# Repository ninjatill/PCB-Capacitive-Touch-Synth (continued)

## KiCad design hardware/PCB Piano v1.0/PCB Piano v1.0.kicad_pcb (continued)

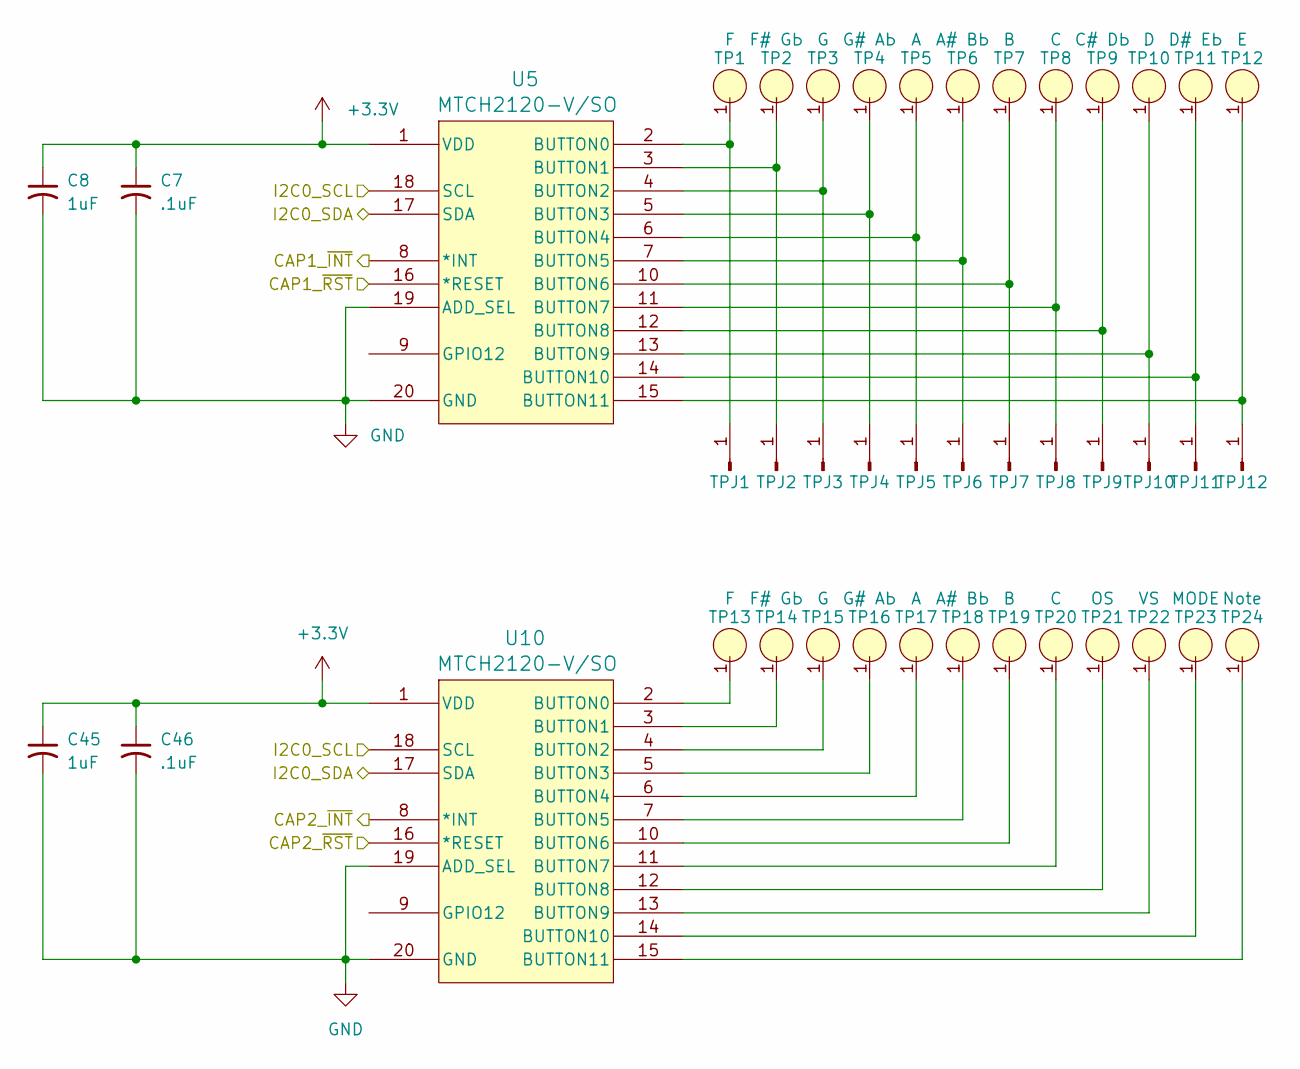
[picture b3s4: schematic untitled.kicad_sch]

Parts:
C7, C46: .1uF; C_0603_1608Metric
C8, C45: 1uF; C_0603_1608Metric
TP1, TP13: F; Touchpad_WhiteKey
TP2, TP14: F# GЬ; Touchpad_BlackKey
TP3, TP15: G; Touchpad_WhiteKey
TP4, TP16: G# AЬ; Touchpad_BlackKey
TP5, TP17: A; Touchpad_WhiteKey
TP6, TP18: A# BЬ; Touchpad_BlackKey
TP7, TP19: B; Touchpad_WhiteKey
TP8, TP20: C; Touchpad_WhiteKey
TP9: C# DЬ; Touchpad_BlackKey
TP10: D; Touchpad_WhiteKey
TP11: D# EЬ; Touchpad_BlackKey
TP12: E; Touchpad_WhiteKey
TP21: OS; Touchpad_Circle_10mm
TP22: VS; Touchpad_Circle_10mm
TP23: MODE; Touchpad_Circle_10mm
TP24: Note
TPJ1, TPJ2, TPJ3, TPJ4, TPJ5, TPJ6, TPJ7, TPJ8, TPJ9, TPJ10, TPJ11, TPJ12: Conn_01x01_Pin
U5, U10: MTCH2120-V/SO; SOIC-20W_7.5x12.8mm_P1.27mm

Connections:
+3.3V: C7.1, C8.1, C45.1, C46.1, U5.1 (VDD), U10.1 (VDD); also elsewhere on the board
/MCU/CAP1_~INT: U5.8 (*INT); also elsewhere on the board
/MCU/CAP1_~RST: U5.16 (*RESET); also elsewhere on the board
/MCU/CAP2_~INT: U10.8 (*INT); also elsewhere on the board
/MCU/CAP2_~RST: U10.16 (*RESET); also elsewhere on the board
/MCU/I2C0_SCL: U5.18 (SCL), U10.18 (SCL); also elsewhere on the board
/MCU/I2C0_SDA: U5.17 (SDA), U10.17 (SDA); also elsewhere on the board
GND: C7.2, C8.2, C45.2, C46.2, U5.19 (ADD_SEL), U5.20 (GND), U10.19 (ADD_SEL), U10.20 (GND); also elsewhere on the board
unnamed: TP1.1, TPJ1.1, U5.2 (BUTTON0)
unnamed: TP2.1, TPJ2.1, U5.3 (BUTTON1)
unnamed: TP3.1, TPJ3.1, U5.4 (BUTTON2)
unnamed: TP4.1, TPJ4.1, U5.5 (BUTTON3)
unnamed: TP5.1, TPJ5.1, U5.6 (BUTTON4)
unnamed: TP6.1, TPJ6.1, U5.7 (BUTTON5)
unnamed: TP7.1, TPJ7.1, U5.10 (BUTTON6)
unnamed: TP8.1, TPJ8.1, U5.11 (BUTTON7)
unnamed: TP9.1, TPJ9.1, U5.12 (BUTTON8)
unnamed: TP10.1, TPJ10.1, U5.13 (BUTTON9)
unnamed: TP11.1, TPJ11.1, U5.14 (BUTTON10)
unnamed: TP12.1, TPJ12.1, U5.15 (BUTTON11)
unnamed: TP13.1, U10.2 (BUTTON0)
unnamed: TP14.1, U10.3 (BUTTON1)
unnamed: TP15.1, U10.4 (BUTTON2)
unnamed: TP16.1, U10.5 (BUTTON3)
unnamed: TP17.1, U10.6 (BUTTON4)
unnamed: TP18.1, U10.7 (BUTTON5)
unnamed: TP19.1, U10.10 (BUTTON6)
unnamed: TP20.1, U10.11 (BUTTON7)
unnamed: TP21.1, U10.12 (BUTTON8)
unnamed: TP22.1, U10.13 (BUTTON9)
unnamed: TP23.1, U10.14 (BUTTON10)
unnamed: TP24.1, U10.15 (BUTTON11)

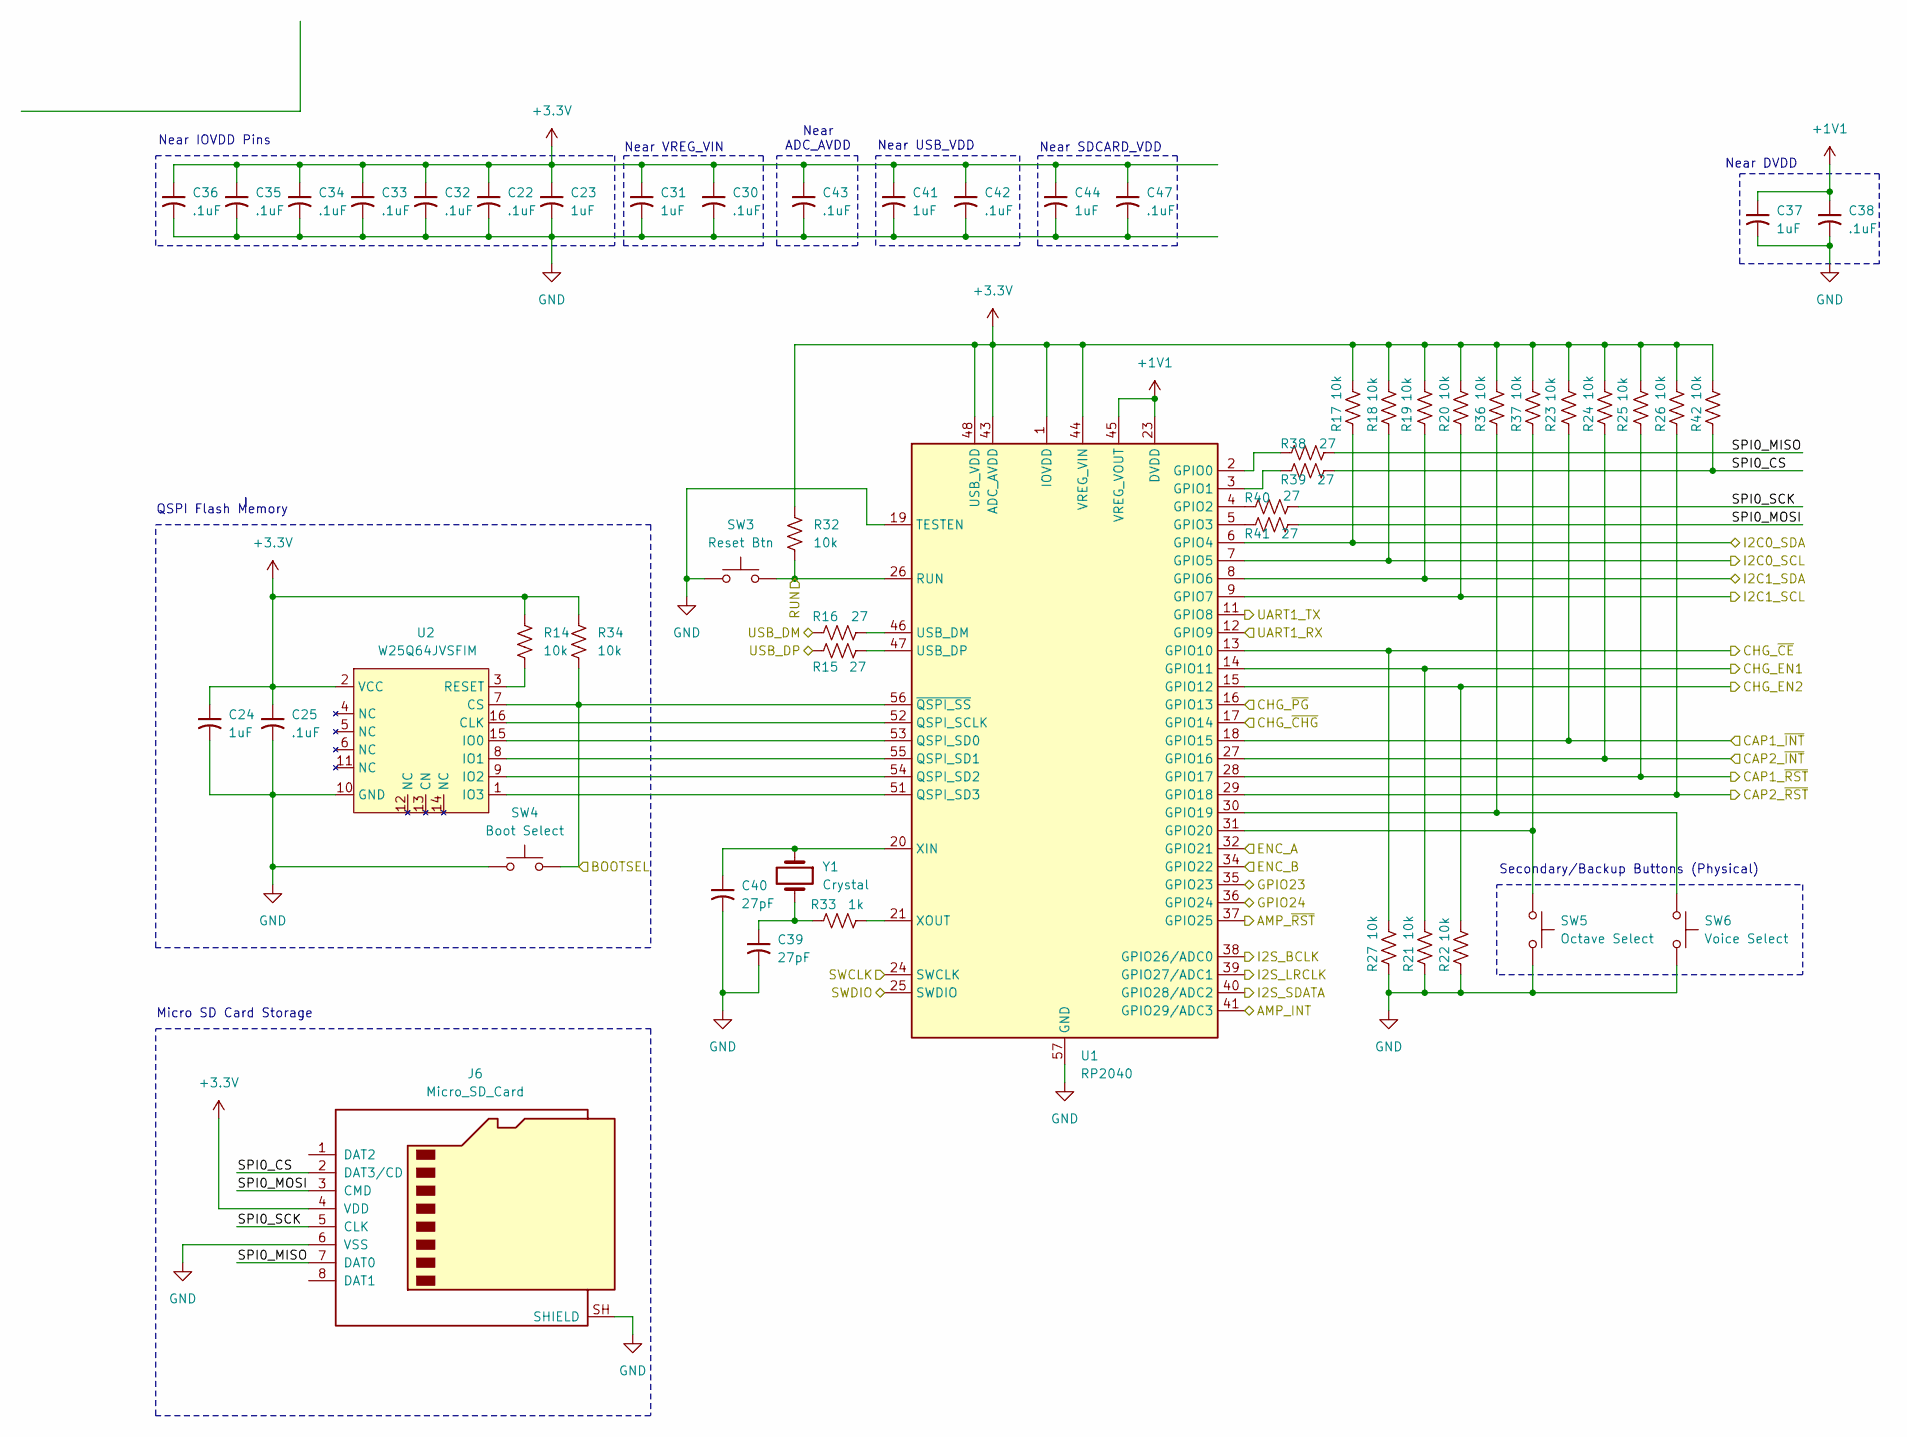
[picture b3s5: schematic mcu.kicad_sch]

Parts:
C22, C25, C30, C32, C33, C34, C35, C36, C38, C42, C43, C47: .1uF; C_0603_1608Metric
C23, C24, C31, C37, C41, C44: 1uF; C_0603_1608Metric
C39, C40: 27pF; C_0603_1608Metric
J6: Micro_SD_Card; microSD_HC_Hirose_DM3D-SF
R14, R17, R18, R19, R20, R21, R22, R23, R24, R25, R26, R27, R32, R34, R36, R37, R42: 10k; R_0603_1608Metric
R15, R16, R38, R39, R40, R41: 27; R_0603_1608Metric
R33: 1k; R_0603_1608Metric
SW3: Reset Btn; Button_Push_KMR6
SW4: Boot Select; Button_Push_KMR6
SW5: Octave Select; Button_Push_KMR6
SW6: Voice Select; Button_Push_KMR6
U1: RP2040; QFN-56-1EP_7x7mm_P0.4mm_EP3.2x3.2mm
U2: W25Q64JVSFIM; SOIC-16W_7.5x10.3mm_P1.27mm
Y1: Crystal; Crystal_SMD_Abracon_ABM8G-4Pin_3.2x2.5mm

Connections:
+1V1: C37.1, C38.1, U1.23 (DVDD), U1.45 (VREG_VOUT), U1.50 (DVDD)
+3.3V: C22.1, C23.1, C24.1, C25.1, C30.1, C31.1, C32.1, C33.1, C34.1, C35.1, C36.1, C41.1, C42.1, C43.1, C44.1, C47.1, J6.4 (VDD), R14.1, R17.1, R18.1, R19.1, R20.1, R23.1, R24.1, R25.1, R26.1, R32.1, R34.1, R36.1, R37.1, R42.1, U1.1 (IOVDD), U1.10 (IOVDD), U1.22 (IOVDD), U1.33 (IOVDD), U1.42 (IOVDD), U1.43 (ADC_AVDD), U1.44 (VREG_VIN), U1.48 (USB_VDD), U1.49 (IOVDD), U2.2 (VCC); also elsewhere on the board
/LED/I2C1_SCL: R20.2, U1.9 (GPIO7); also elsewhere on the board
/LED/I2C1_SDA: R19.2, U1.8 (GPIO6); also elsewhere on the board
/MCU/AMP_INT: U1.41 (GPIO29/ADC3); also elsewhere on the board
/MCU/AMP_~RST: U1.37 (GPIO25); also elsewhere on the board
/MCU/BOOTSEL: R34.2, SW4.2, U1.56 (~QSPI_SS), U2.7 (CS); also elsewhere on the board
/MCU/CAP1_~INT: R23.2, U1.18 (GPIO15); also elsewhere on the board
/MCU/CAP1_~RST: R25.2, U1.28 (GPIO17); also elsewhere on the board
/MCU/CAP2_~INT: R24.2, U1.27 (GPIO16); also elsewhere on the board
/MCU/CAP2_~RST: R26.2, U1.29 (GPIO18); also elsewhere on the board
/MCU/CHG_EN1: R21.1, U1.14 (GPIO11); also elsewhere on the board
/MCU/CHG_EN2: R22.1, U1.15 (GPIO12); also elsewhere on the board
/MCU/CHG_~CE: R27.1, U1.13 (GPIO10); also elsewhere on the board
/MCU/CHG_~CHG: U1.17 (GPIO14); also elsewhere on the board
/MCU/CHG_~PG: U1.16 (GPIO13); also elsewhere on the board
/MCU/ENC_A: U1.32 (GPIO21); also elsewhere on the board
/MCU/ENC_B: U1.34 (GPIO22); also elsewhere on the board
/MCU/GPIO23: U1.35 (GPIO23); also elsewhere on the board
/MCU/GPIO24: U1.36 (GPIO24); also elsewhere on the board
/MCU/I2C0_SCL: R18.2, U1.7 (GPIO5); also elsewhere on the board
/MCU/I2C0_SDA: R17.2, U1.6 (GPIO4); also elsewhere on the board
/MCU/I2S_BCLK: U1.38 (GPIO26/ADC0); also elsewhere on the board
/MCU/I2S_LRCLK: U1.39 (GPIO27/ADC1); also elsewhere on the board
/MCU/I2S_SDATA: U1.40 (GPIO28/ADC2); also elsewhere on the board
/MCU/SPI0_CS: J6.2 (DAT3/CD), R39.1, R42.2
/MCU/SPI0_MISO: J6.7 (DAT0), R38.1
/MCU/SPI0_MOSI: J6.3 (CMD), R41.1
/MCU/SPI0_SCK: J6.5 (CLK), R40.1
/MCU/SWCLK: U1.24 (SWCLK); also elsewhere on the board
/MCU/UART1_RX: U1.12 (GPIO9); also elsewhere on the board
/MCU/UART1_TX: U1.11 (GPIO8); also elsewhere on the board
/MCU/USB_DM: R16.2; also elsewhere on the board
/MCU/USB_DP: R15.2; also elsewhere on the board
/debug/RUN: R32.2, SW3.2, U1.26 (RUN); also elsewhere on the board
/debug/SWDIO: U1.25 (SWDIO); also elsewhere on the board
GND: C22.2, C23.2, C24.2, C25.2, C30.2, C31.2, C32.2, C33.2, C34.2, C35.2, C36.2, C37.2, C38.2, C39.2, C40.2, C41.2, C42.2, C43.2, C44.2, C47.2, J6.6 (VSS), J6.SH (SHIELD), R21.2, R22.2, R27.2, SW3.1, SW4.1, SW5.2, SW6.2, U1.19 (TESTEN), U1.57 (GND), U2.10 (GND); also elsewhere on the board
unnamed: C39.1, R33.1, Y1.2
unnamed: R38.2, U1.2 (GPIO0)
unnamed: R39.2, U1.3 (GPIO1)
unnamed: R40.2, U1.4 (GPIO2)
unnamed: R41.2, U1.5 (GPIO3)
unnamed: R36.2, SW6.1, U1.30 (GPIO19)
unnamed: R37.2, SW5.1, U1.31 (GPIO20)
unnamed: U1.52 (QSPI_SCLK), U2.16 (CLK)
unnamed: U1.53 (QSPI_SD0), U2.15 (IO0)
unnamed: U1.55 (QSPI_SD1), U2.8 (IO1)
unnamed: U1.54 (QSPI_SD2), U2.9 (IO2)
unnamed: U1.51 (QSPI_SD3), U2.1 (IO3)
unnamed: R16.1, U1.46 (USB_DM)
unnamed: R15.1, U1.47 (USB_DP)
unnamed: C40.1, U1.20 (XIN), Y1.1
unnamed: R33.2, U1.21 (XOUT)
unnamed: R14.2, U2.3 (RESET)

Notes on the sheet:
Near VREG_VIN
Near DVDD
Near IOVDD Pins
Secondary/Backup Buttons (Physical)
Micro SD Card Storage
Near USB_VDD
Near ADC_AVDD
Near SDCARD_VDD
QSPI Flash Memory

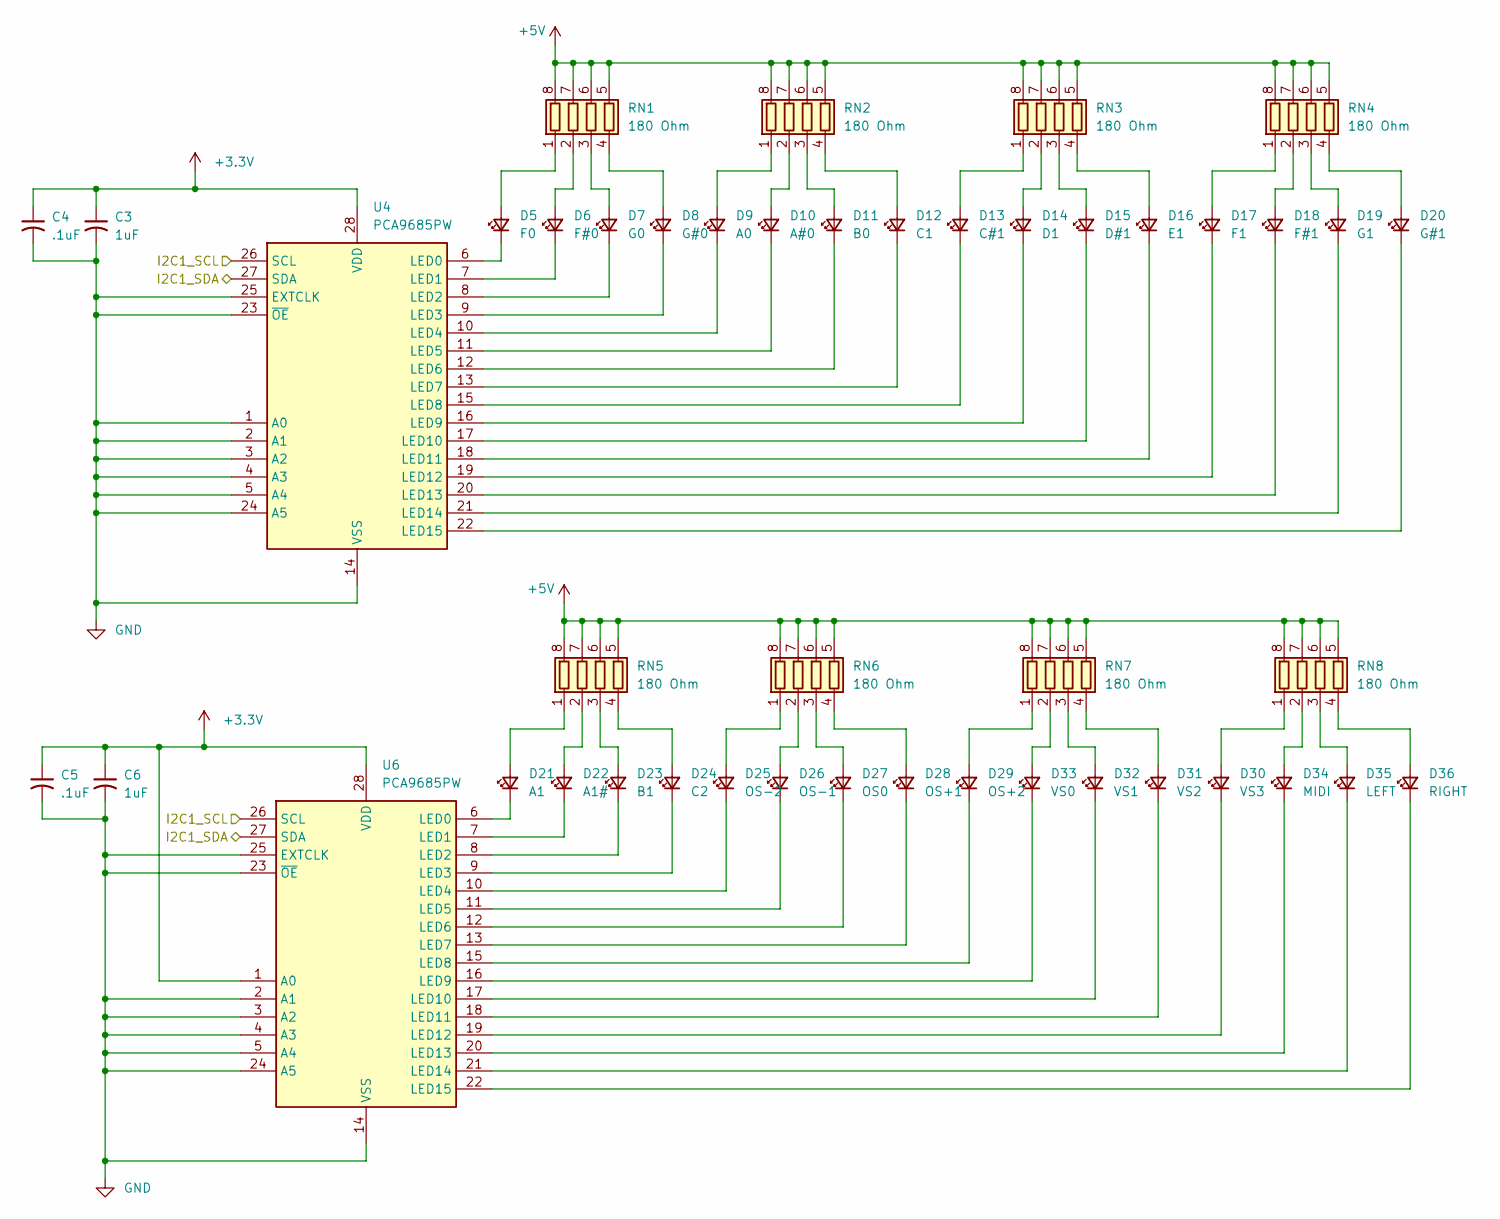
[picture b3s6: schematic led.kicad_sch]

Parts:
C3, C6: 1uF; C_0603_1608Metric
C4, C5: .1uF; C_0603_1608Metric
D5: F0; LED_0603_1608Metric
D6: F#0; LED_0603_1608Metric
D7: G0; LED_0603_1608Metric
D8: G#0; LED_0603_1608Metric
D9: A0; LED_0603_1608Metric
D10: A#0; LED_0603_1608Metric
D11: B0; LED_0603_1608Metric
D12: C1; LED_0603_1608Metric
D13: C#1; LED_0603_1608Metric
D14: D1; LED_0603_1608Metric
D15: D#1; LED_0603_1608Metric
D16: E1; LED_0603_1608Metric
D17: F1; LED_0603_1608Metric
D18: F#1; LED_0603_1608Metric
D19: G1; LED_0603_1608Metric
D20: G#1; LED_0603_1608Metric
D21: A1; LED_0603_1608Metric
D22: A1#; LED_0603_1608Metric
D23: B1; LED_0603_1608Metric
D24: C2; LED_0603_1608Metric
D25: OS-2; LED_0603_1608Metric
D26: OS-1; LED_0603_1608Metric
D27: OS0; LED_0603_1608Metric
D28: OS+1; LED_0603_1608Metric
D29: OS+2; LED_0603_1608Metric
D30: VS3; LED_0603_1608Metric
D31: VS2; LED_0603_1608Metric
D32: VS1; LED_0603_1608Metric
D33: VS0; LED_0603_1608Metric
D34: MIDI; LED_0603_1608Metric
D35: LEFT; LED_0603_1608Metric
D36: RIGHT; LED_0603_1608Metric
RN1, RN2, RN3, RN4, RN5, RN6, RN7, RN8: 180 Ohm; R_Array_Convex_4x1206
U4, U6: PCA9685PW; TSSOP-28_4.4x9.7mm_P0.65mm

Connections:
+3.3V: C3.1, C4.1, C5.1, C6.1, U4.28 (VDD), U6.1 (A0), U6.28 (VDD); also elsewhere on the board
+5V: RN1.5 (R4.2), RN1.6 (R3.2), RN1.7 (R2.2), RN1.8 (R1.2), RN2.5 (R4.2), RN2.6 (R3.2), RN2.7 (R2.2), RN2.8 (R1.2), RN3.5 (R4.2), RN3.6 (R3.2), RN3.7 (R2.2), RN3.8 (R1.2), RN4.5 (R4.2), RN4.6 (R3.2), RN4.7 (R2.2), RN4.8 (R1.2), RN5.5 (R4.2), RN5.6 (R3.2), RN5.7 (R2.2), RN5.8 (R1.2), RN6.5 (R4.2), RN6.6 (R3.2), RN6.7 (R2.2), RN6.8 (R1.2), RN7.5 (R4.2), RN7.6 (R3.2), RN7.7 (R2.2), RN7.8 (R1.2), RN8.5 (R4.2), RN8.6 (R3.2), RN8.7 (R2.2), RN8.8 (R1.2); also elsewhere on the board
/LED/I2C1_SCL: U4.26 (SCL), U6.26 (SCL); also elsewhere on the board
/LED/I2C1_SDA: U4.27 (SDA), U6.27 (SDA); also elsewhere on the board
GND: C3.2, C4.2, C5.2, C6.2, U4.1 (A0), U4.2 (A1), U4.3 (A2), U4.4 (A3), U4.5 (A4), U4.14 (VSS), U4.23 (~OE), U4.24 (A5), U4.25 (EXTCLK), U6.2 (A1), U6.3 (A2), U6.4 (A3), U6.5 (A4), U6.14 (VSS), U6.23 (~OE), U6.24 (A5), U6.25 (EXTCLK); also elsewhere on the board
unnamed: D5.2 (A), RN1.1 (R1.1)
unnamed: D5.1 (K), U4.6 (LED0)
unnamed: D6.2 (A), RN1.2 (R2.1)
unnamed: D6.1 (K), U4.7 (LED1)
unnamed: D7.2 (A), RN1.3 (R3.1)
unnamed: D7.1 (K), U4.8 (LED2)
unnamed: D8.2 (A), RN1.4 (R4.1)
unnamed: D8.1 (K), U4.9 (LED3)
unnamed: D9.2 (A), RN2.1 (R1.1)
unnamed: D9.1 (K), U4.10 (LED4)
unnamed: D10.2 (A), RN2.2 (R2.1)
unnamed: D10.1 (K), U4.11 (LED5)
unnamed: D11.2 (A), RN2.3 (R3.1)
unnamed: D11.1 (K), U4.12 (LED6)
unnamed: D12.2 (A), RN2.4 (R4.1)
unnamed: D12.1 (K), U4.13 (LED7)
unnamed: D13.2 (A), RN3.1 (R1.1)
unnamed: D13.1 (K), U4.15 (LED8)
unnamed: D14.2 (A), RN3.2 (R2.1)
unnamed: D14.1 (K), U4.16 (LED9)
unnamed: D15.2 (A), RN3.3 (R3.1)
unnamed: D15.1 (K), U4.17 (LED10)
unnamed: D16.2 (A), RN3.4 (R4.1)
unnamed: D16.1 (K), U4.18 (LED11)
unnamed: D17.2 (A), RN4.1 (R1.1)
unnamed: D17.1 (K), U4.19 (LED12)
unnamed: D18.2 (A), RN4.2 (R2.1)
unnamed: D18.1 (K), U4.20 (LED13)
unnamed: D19.2 (A), RN4.3 (R3.1)
unnamed: D19.1 (K), U4.21 (LED14)
unnamed: D20.2 (A), RN4.4 (R4.1)
unnamed: D20.1 (K), U4.22 (LED15)
unnamed: D21.2 (A), RN5.1 (R1.1)
unnamed: D21.1 (K), U6.6 (LED0)
unnamed: D22.2 (A), RN5.2 (R2.1)
unnamed: D22.1 (K), U6.7 (LED1)
unnamed: D23.2 (A), RN5.3 (R3.1)
unnamed: D23.1 (K), U6.8 (LED2)
unnamed: D24.2 (A), RN5.4 (R4.1)
unnamed: D24.1 (K), U6.9 (LED3)
unnamed: D25.2 (A), RN6.1 (R1.1)
unnamed: D25.1 (K), U6.10 (LED4)
unnamed: D26.2 (A), RN6.2 (R2.1)
unnamed: D26.1 (K), U6.11 (LED5)
unnamed: D27.2 (A), RN6.3 (R3.1)
unnamed: D27.1 (K), U6.12 (LED6)
unnamed: D28.2 (A), RN6.4 (R4.1)
unnamed: D28.1 (K), U6.13 (LED7)
unnamed: D29.2 (A), RN7.1 (R1.1)
unnamed: D29.1 (K), U6.15 (LED8)
unnamed: D30.2 (A), RN8.1 (R1.1)
unnamed: D30.1 (K), U6.19 (LED12)
unnamed: D31.2 (A), RN7.4 (R4.1)
unnamed: D31.1 (K), U6.18 (LED11)
unnamed: D32.2 (A), RN7.3 (R3.1)
unnamed: D32.1 (K), U6.17 (LED10)
unnamed: D33.2 (A), RN7.2 (R2.1)
unnamed: D33.1 (K), U6.16 (LED9)
unnamed: D34.2 (A), RN8.2 (R2.1)
unnamed: D34.1 (K), U6.20 (LED13)
unnamed: D35.2 (A), RN8.3 (R3.1)
unnamed: D35.1 (K), U6.21 (LED14)
unnamed: D36.2 (A), RN8.4 (R4.1)
unnamed: D36.1 (K), U6.22 (LED15)

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
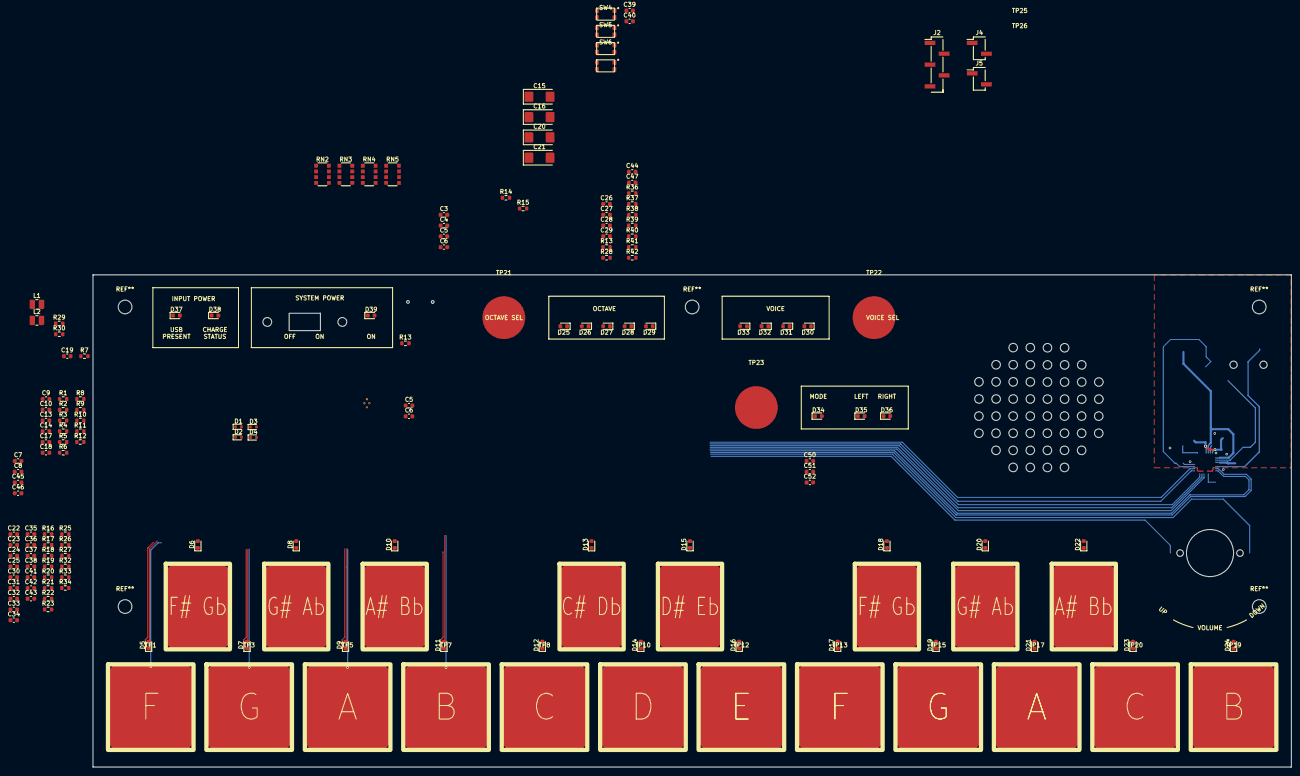
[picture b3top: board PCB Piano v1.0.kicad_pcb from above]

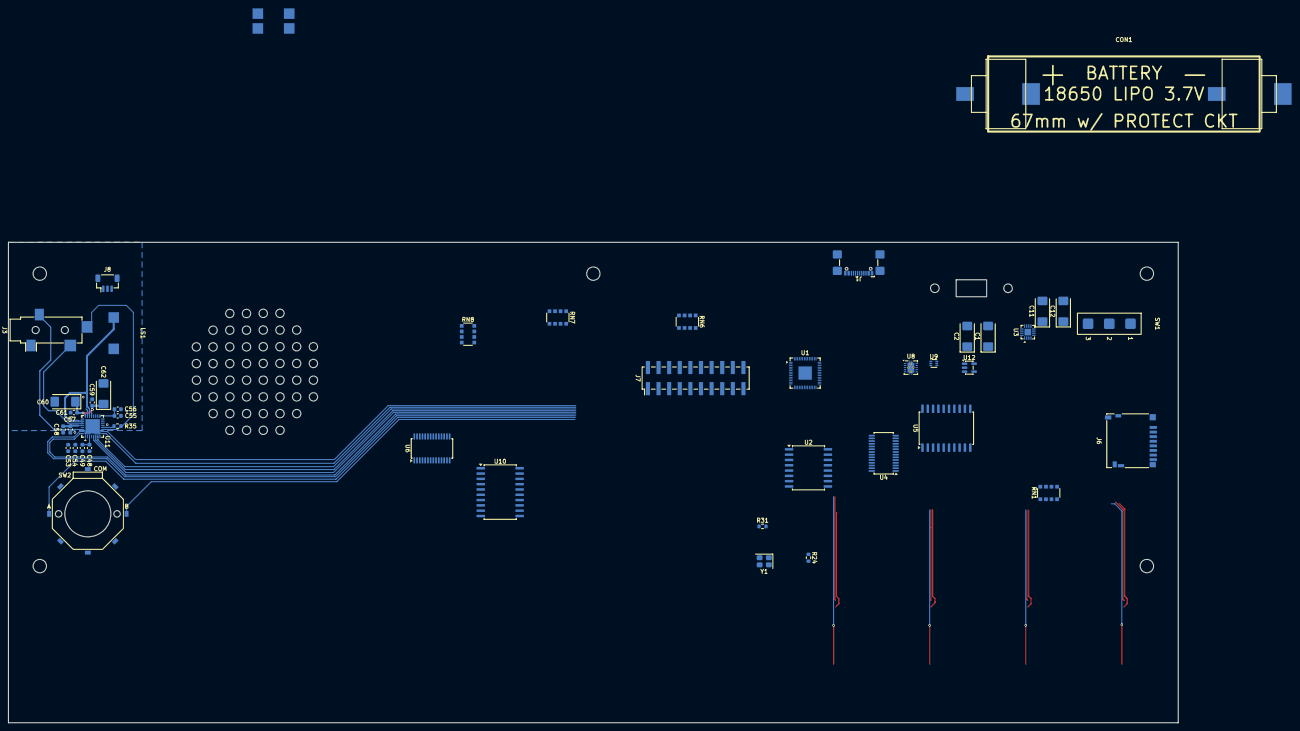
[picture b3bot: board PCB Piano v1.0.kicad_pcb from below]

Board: 2 copper layers, 280.0 x 115.0 mm, 209 parts (44 on the bottom side), 171 nets.

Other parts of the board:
C5#2, C26: .1uF; C_0603_1608Metric
C6#2, C27: 1uF; C_0603_1608Metric
R13#2: 1.5k; R_0603_1608Metric

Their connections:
+3.3V: C5#2.1, C6#2.1; also elsewhere on the board
+5V: C26.1, C27.1; also elsewhere on the board
GND: C5#2.2, C6#2.2, C26.2, C27.2; also elsewhere on the board

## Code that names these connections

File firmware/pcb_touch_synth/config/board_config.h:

#pragma once

// ======================================================
// BOARD PIN CONFIGURATION
//
// Central GPIO pin map for the PCB Piano RP2040 board.
// All peripheral drivers reference these defines — change
// a pin here and it propagates to the entire firmware.
//
// Hardware overview:
//   MCU:     RP2040 (dual-core Cortex-M0+, 133MHz)
//   Flash:   128Mbit QSPI external flash
//   I2C0:    Touch controllers    (PIN_I2C0_SDA / PIN_I2C0_SCL)
//   I2C1:    Audio, Power, LEDs   (PIN_I2C1_SDA / PIN_I2C1_SCL)
//   SPI0:    SD card + DotStar LEDs share bus
//            (PIN_SPI0_SCK / PIN_SPI0_TX / PIN_SPI0_RX / PIN_SPI0_CS_SD)
//            DotStar uses PIN_DOTSTAR_CLK / PIN_DOTSTAR_DATA (same physical pins as SPI0 SCK/TX)
//   SD det:  PIN_SD_CARD_DETECT — active-LOW, 10kΩ pull-up on PCB
//   I2S out: DAC audio output  (PIN_AUDIO_I2S_BCLK / PIN_AUDIO_I2S_LRCLK / PIN_AUDIO_I2S_DATA)
//   I2S in:  MEMS mic input    (PIN_MIC_I2S_DATA, shares BCLK/LRCLK with the DAC output)
//   UART:    Debug header       (UART_TX_PIN / UART_RX_PIN, not yet enabled in firmware)
//
// GPIO ALLOCATION SUMMARY (RP2040 GPIO 0-29)
//   0  SPI0_RX       1  SPI0_CS_SD    2  SPI0_SCK/DOTSTAR_CLK  3  SPI0_TX/DOTSTAR_DATA
//   4  I2C0_SDA      5  I2C0_SCL      6  I2C1_SDA              7  I2C1_SCL
//   8  SD_CARD_DETECT  9  CHARGER_IRQ  10  USB_MUX_SEL         11  DEBUG_GPIO11
//  12  UART_TX       13 UART_RX       14  (unassigned)          15  TOUCH1_IRQ
//  16  TOUCH2_IRQ   17  TOUCH_RESET  18  DOTSTAR_ENABLE         19  5V_EN
//  20  LED_EN        21 AUDIO_VOL_A  22  AUDIO_VOL_B            23  MIC_I2S_DATA
//  24  DEBUG_GPIO24  25 AUDIO_RESET  26  AUDIO_I2S_BCLK         27  AUDIO_I2S_LRCLK
//  28  AUDIO_I2S_DATA  29 AUDIO_IRQ
// ======================================================

// ======================================================
// I2C BUSES
// ======================================================

// I2C0
#define PIN_I2C0_SDA    4
#define PIN_I2C0_SCL    5

// I2C1
#define PIN_I2C1_SDA    6
#define PIN_I2C1_SCL    7

// ======================================================
// SPI BUS
// ======================================================

#define PIN_SPI0_SCK    2
#define PIN_SPI0_TX     3
#define PIN_SPI0_RX     0
#define PIN_SPI0_CS_SD  1

// ======================================================
// DOTSTAR STATUS LEDS
// ======================================================

#define PIN_DOTSTAR_CLK     2
#define PIN_DOTSTAR_DATA    3
#define PIN_DOTSTAR_ENABLE  18

// ======================================================
// LED CONTROLLERS
// ======================================================

#define PIN_LED_EN      20

// ======================================================
// TOUCH CONTROLLER
// ======================================================

#define PIN_TOUCH1_IRQ    15
#define PIN_TOUCH2_IRQ    16
#define PIN_TOUCH_RESET   17

// ======================================================
// AUDIO
// ======================================================

#define PIN_AUDIO_I2S_BCLK      26
#define PIN_AUDIO_I2S_LRCLK     27
#define PIN_AUDIO_I2S_DATA      28
#define PIN_AUDIO_RESET         25
#define PIN_AUDIO_IRQ           29

#define PIN_AUDIO_VOL_A         21
#define PIN_AUDIO_VOL_B         22

// ======================================================
// MICROPHONE I2S INPUT (ICS-43432)
//
// PIN_MIC_I2S_DATA is the mic's SD output (data back to RP2040).
// The mic shares PIN_AUDIO_I2S_BCLK and PIN_AUDIO_I2S_LRCLK with
// the TLV320DAC3100 DAC — both devices see the same BCLK and WCLK
// from the RP2040 I2S master at AUDIO_BCLK_HZ (44100 × 64 = 2,822,400 Hz).
//
// Hardwired on PCB (no MCU GPIO needed):
//   CONFIG pin → GND   (required by ICS-43432 datasheet)
//   LR pin     → 3V3   (mic outputs on RIGHT channel; data follows WS rising edge)
// The SD line has a 100kΩ pull-down to GND (confirmed on PCB).
// ======================================================

#define PIN_MIC_I2S_DATA        23

// ======================================================
// BATTERY CHARGER / POWER PATH
// ======================================================

#define PIN_CHARGER_IRQ          9
#define PIN_USB_MUX_SEL         10
#define PIN_5V_EN               19

// ======================================================
// SD CARD
//
// PIN_SD_DETECT: mechanical card-detect switch in the SD slot.
// Active-LOW: card inserted = LOW, card absent = HIGH.
// Circuit: GPIO → 10kΩ pull-up to 3.3V (on PCB) → switch → GND.
// Configure as GPIO_IN with internal pull-up DISABLED (pull-up is external).
// Can be used for edge-triggered interrupt on card insert/remove.
// ======================================================

#define PIN_SD_CARD_DETECT   8

// ======================================================
// FUTURE USE / HARDWARE ALLOCATIONS ON PCB (not yet implemented in firmware)
// ======================================================

#define UART_TX_PIN         12
#define UART_RX_PIN         13
#define DEBUG_GPIO11        11
#define DEBUG_GPIO24        24

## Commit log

2026-05-11 Development Phase - Initial github push.
    Initial github push. Still in development. Nothing finalized. Schematic 95% complete. Starting PCB organization and layout; only piano keys are final size and placement.
2026-05-12 PCB work - v0.1
    PCB Work v0.1. Moved audio Amp and AGND to top right corner.
2026-05-14 Development Phase Update
    PCB layout refined more, still not complete. Trying to start a separate v1.1 PCB file to explore a 4-layer PCB.
2026-05-15 Development Step
    More PCB Layout work completed. Added MEMS microphone. Moved around debug connector signals. Changed Speaker to just a cut out (will 3D print a grille to go into cutout.)
2026-05-18 Development Phase - PCB Complete - ERC/DRC in progress
    Development commit. PBC layout complete. ERC/DRC checks in progress. Swapped some connectors for JST connectors with Adafruit-style polarization.
2026-06-01 Firmware architecture complete - PCB revision with new charger.
    Firmware Architecture Complete
    - Added MP2724 charger driver
    - Added TLV320DAC3100 driver
    - Added MTCH2120 touch driver
    - Added PCA9685 driver
    - Added DotStar driver
2026-06-01 I2C address file tweak.
    Just reorganizing I2C address file.
2026-06-09 PCB Finalized and Ordered. Firmware near completion.
    PCB Finalized and Ordered. Final revisions included fixing bugs on some peripheral chips. Also added an RTC circuit after realizing the SD card could benefit from adding file timestamps.
    Firmware near completion. Still need to finalize some SD card operations. Synth audio core is finished and all the board peripheral chip drivers were completed.
2026-06-19 Tweaks. Just to fab layer.
    Tweaks. Just to fab layer.
